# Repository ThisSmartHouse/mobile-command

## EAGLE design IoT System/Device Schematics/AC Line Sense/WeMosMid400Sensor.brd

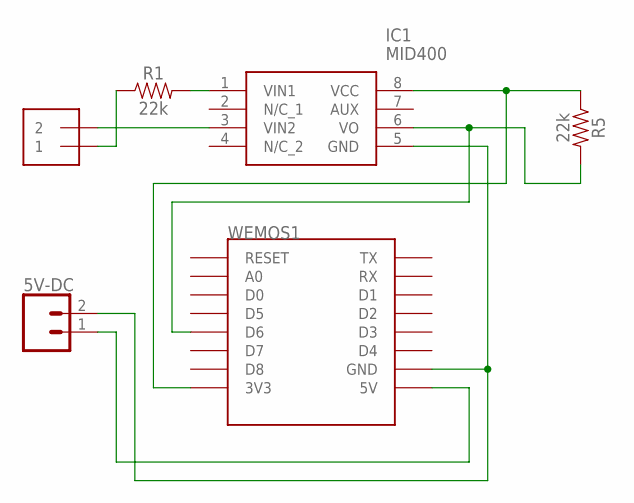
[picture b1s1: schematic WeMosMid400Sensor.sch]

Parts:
5V-DC: CONN_02; 1X02
A/C: 1X2-3.5MM
IC1: MID400; DIP762W56P254L966H508Q8N
R1, R5: 22k; AXIAL-0.3
WEMOS1: WEMOS-D1-MINI

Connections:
unnamed: A/C.1, R1.P$1 (1)
unnamed: A/C.2, IC1.3 (VIN2)
unnamed: IC1.1 (VIN1), R1.P$2 (2)
unnamed: 5V-DC.1, WEMOS1.5V
unnamed: IC1.6 (VO), R5.P$2 (2), WEMOS1.D6
unnamed: IC1.8 (VCC), R5.P$1 (1), WEMOS1.3V3
unnamed: 5V-DC.2, IC1.5 (GND), WEMOS1.GND

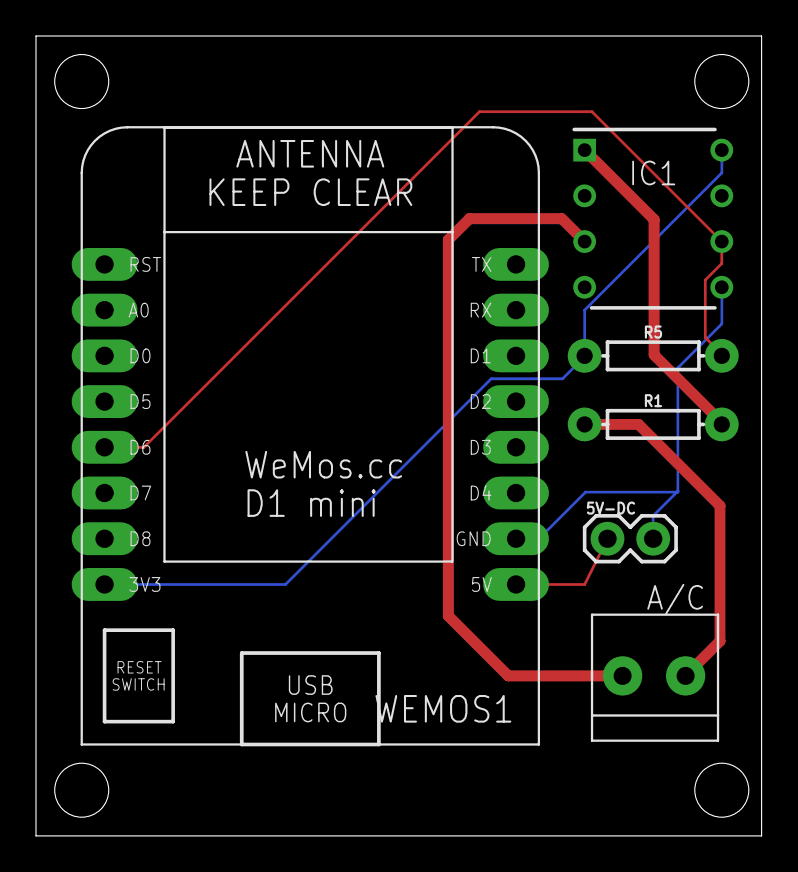
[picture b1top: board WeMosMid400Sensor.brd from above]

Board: 2 copper layers, 40.3 x 44.4 mm, 6 parts (0 on the bottom side), 7 nets.

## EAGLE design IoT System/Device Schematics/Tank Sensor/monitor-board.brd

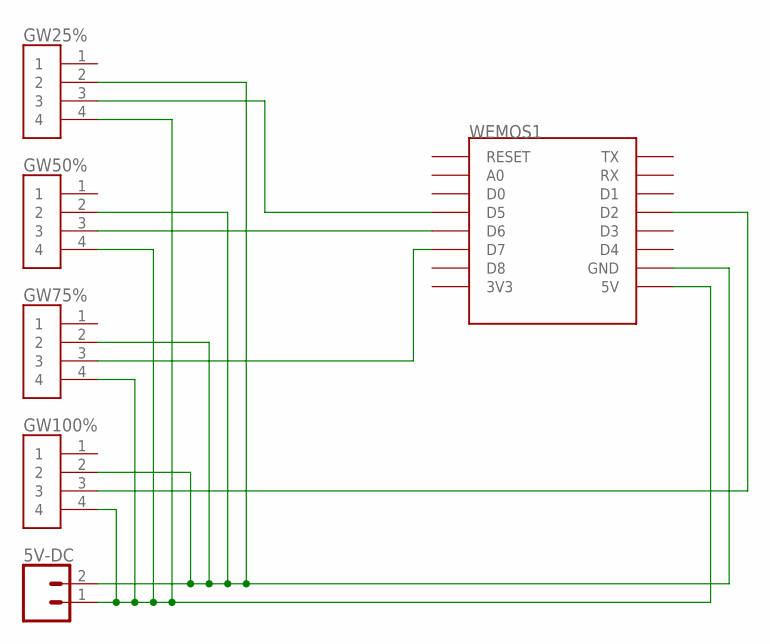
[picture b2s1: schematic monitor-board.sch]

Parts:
5V-DC: CONN_02; 1X02
GW25%, GW50%, GW75%, GW100%: B4B-XH-A(LF)(SN); JST_B4B-XH-A(LF)(SN)
WEMOS1: WEMOS-D1-MINI

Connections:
unnamed: 5V-DC.1, GW25%.4, GW50%.4, GW75%.4, GW100%.4, WEMOS1.5V
unnamed: 5V-DC.2, GW25%.2, GW50%.2, GW75%.2, GW100%.2, WEMOS1.GND
unnamed: GW25%.3, WEMOS1.D5
unnamed: GW100%.3, WEMOS1.D2
unnamed: GW75%.3, WEMOS1.D7
unnamed: GW50%.3, WEMOS1.D6

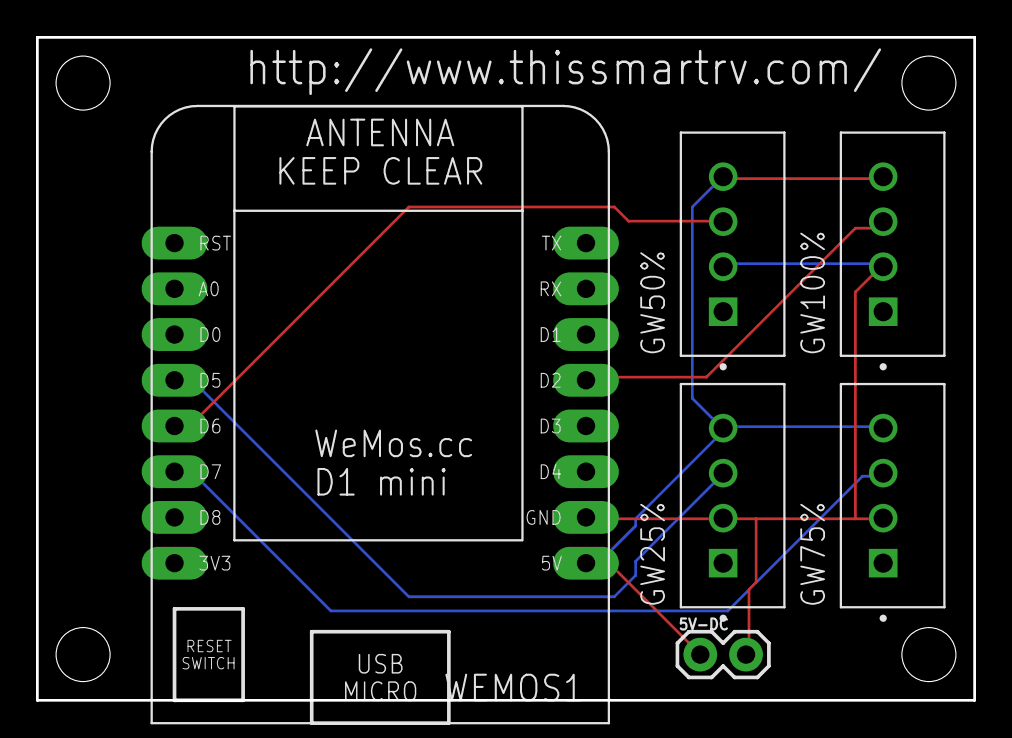
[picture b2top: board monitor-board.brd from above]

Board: 2 copper layers, 52.1 x 36.8 mm, 6 parts (0 on the bottom side), 6 nets.

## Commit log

2019-08-27 Adding the initial versions of the various supporting documents I've been working on
2019-08-27 Adding .gitignore
2019-08-28 Updating the RV model and adding the drawing for the Water System layout
2019-09-16 Adding a bunch of 3D models of things I printed for the rig Adding schematic documents for the Cobra 1500W inverter, specifically the remote control port I got from their support team Adding a small 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
2019-10-08 Reorganizing the files so they make more sense as they were getting a bit unruly.
2020-04-19 Adding new models, plans, schematics, etc.
2020-04-19 Combining Electrical Panels into one file and fixing them up a bit.
2020-04-19 More cleaning up of electrical panels
2020-04-19 More cleanup on Panels, and adding laser-ready designs for top panel
2020-04-21 Adding a ghost wire terminal design
2020-04-26 Adding Ghostwire terminal STL and adding the current sensor to the hub panel

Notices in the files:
parts and their libraries:
SparkFun-Connectors: Licensing: Creative Commons ShareAlike 4.0 International - https://creativecommons.org/licenses/by-sa/4.0
